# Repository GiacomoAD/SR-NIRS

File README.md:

# SR-NIRS
> Started on Jan/2021

SR-NIRS is a project to develop a low cost, portable, Spatially Resolved Near-Infrared Spectroscopy embedded system. Currently, the project is based on ESP-32 microcontroller.

The goal is to be able to monitor Tissue Oxygenation Index (TOI) from the forearm muscle during arm arterial occlusion experiment in a real time application.

The project also includes the development of a *Python GUI* to interact with the system.

*Undergraduate Final Project*

## Python GUI

This system was developed along with a Python GUI to enable wireless (currently Bluetooth) communication and data logging, as well as user monitoring of the incoming NIRS signal.

****

### Setup - Python Virtual Environment  

**This step, even though recommended, is not required. You can skip to Python Requirements sections if you wish.**

First of all, it is recommended to create a Python Virtual Environment. This can be done through python's embedded  (v. 3.4+) module called **venv**:

```
python -m venv [directory]
``` 

Then, the environment should be activated through:  
- ### Windows  
``` 
[directory]\Scripts\activate.bat
```

- ### Linux or MacOS  
```
source [directory]/bin/activate 
``` 

[More information on python virtual environments can be found here.](https://python.land/virtual-environments/virtualenv)

### Setup - Python Requirements

All of the required packages are included on **_requirements.txt_** file, inside **_GUI_** folder.  

These requirements can be installed through python's **pip** module, as it follows:

```
pip install -r requirements.txt
``` 

### Running GUI

To run the system GUI, the **_main.py_** script should be executed:
```
python main.py
``` 

***
## Documentation

The documentation will be in included in this repository as the project progresses.

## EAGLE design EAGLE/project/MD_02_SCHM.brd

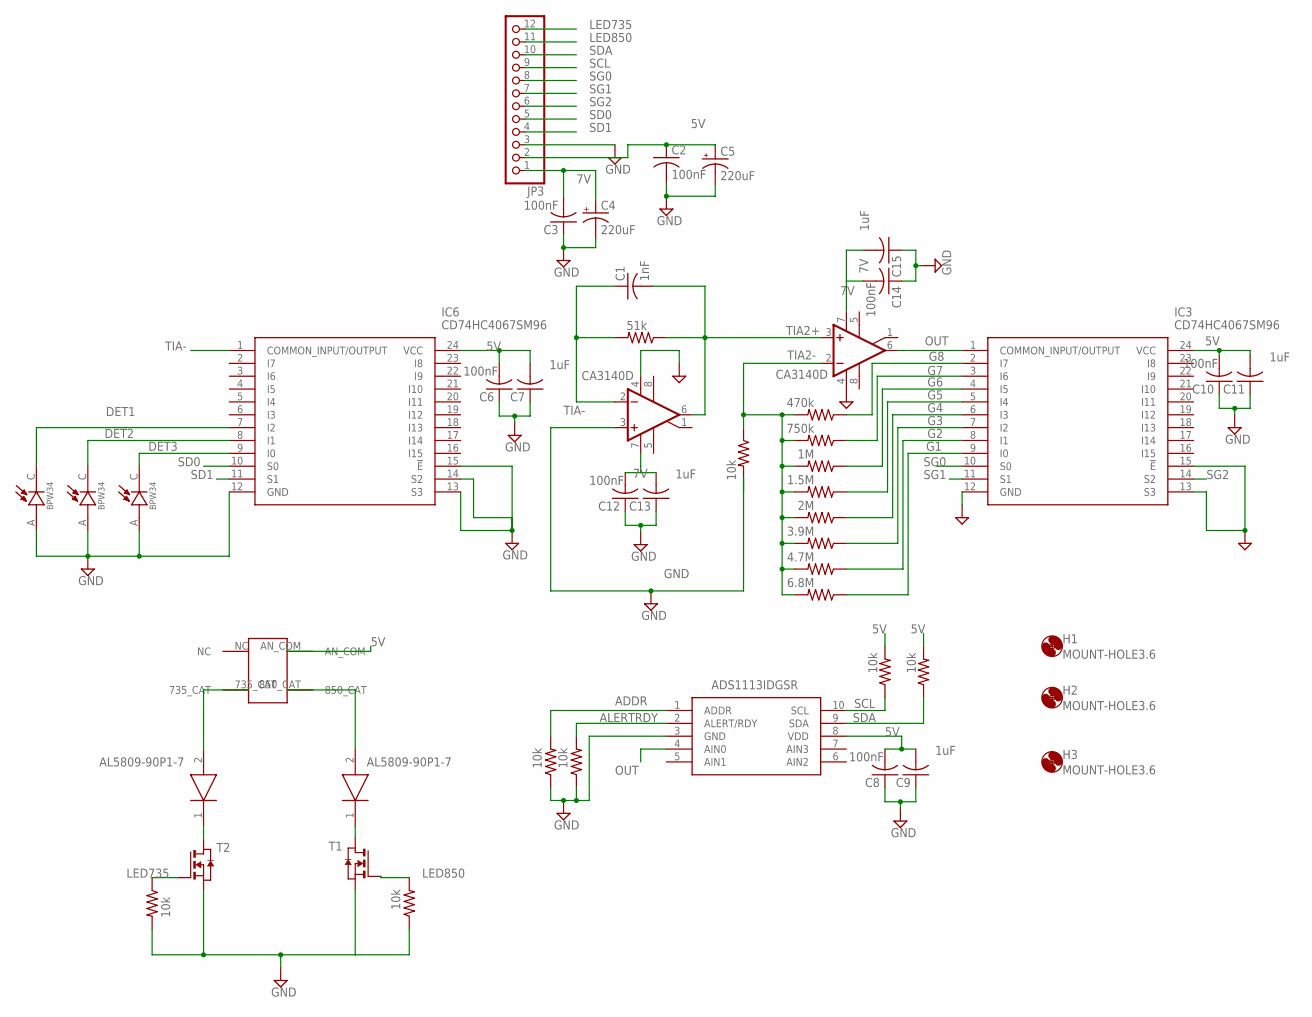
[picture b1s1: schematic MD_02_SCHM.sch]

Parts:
C1: 1nF; C0805
C2, C3, C6, C8, C10, C12, C14: 100nF; C0805
C4, C5: 220uF; E5-6
C7, C9, C11, C13, C15: 1uF; C0805
D1, D5: AL5809-90P1-7; SODFL3718X100N
D2, D3, D4: BPW34; DIO_BPW34
H1, H2, H3: MOUNT-HOLE3.6; 3,6
IC1, IC2: CA3140D; SO08
IC3, IC6: CD74HC4067SM96; SOP65P780X200-24N
IC5: ADS1113IDGSR; SOP50P490X110-10N
JP3: PINHD-1X12; 1X12
R1: 51k; R0805
R2, R11, R12, R13, R14, R15, R16: 10k; R0805
R3: 470k; R0805
R4: 750k; R0805
R5: 1M; R0805
R6: 1.5M; R0805
R7: 2M; R0805
R8: 3.9M; R0805
R9: 4.7M; R0805
R10: 6.8M; R0805
T1, T2: NMOSSOT23; SOT-23
U$1: SMT735D_850D

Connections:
5V: C2.1, C5.+, C6.2, C7.2, C8.2, C9.2, C10.2, C11.2, IC3.24 (VCC), IC5.8 (VDD), IC6.24 (VCC), JP3.2, R13.2, R14.2, U$1.AN_COM
7V: C3.2, C4.+, C12.2, C13.2, C14.2, C15.2, IC1.7 (V+), IC2.7 (V+), JP3.1
ADDR: IC5.1 (ADDR), R11.2
ALERTRDY: IC5.2 (ALERT/RDY), R12.2
DET1: D2.C, IC6.7 (I2)
DET2: D3.C, IC6.8 (I1)
DET3: D4.C, IC6.9 (I0)
G1: IC3.9 (I0), R10.1
G2: IC3.8 (I1), R9.1
G3: IC3.7 (I2), R8.1
G4: IC3.6 (I3), R7.1
G5: IC3.5 (I4), R6.1
G6: IC3.4 (I5), R5.1
G7: IC3.3 (I6), R4.1
G8: IC3.2 (I7), R3.1
GND: C2.2, C3.1, C4.-, C5.-, C6.1, C7.1, C8.1, C9.1, C10.1, C11.1, C12.1, C13.1, C14.1, C15.1, D2.A, D3.A, D4.A, IC1.3 (+IN), IC1.4 (V-), IC2.4 (V-), IC3.12 (GND), IC3.13 (S3), IC3.15 (!E), IC5.3 (GND), IC6.12 (GND), IC6.13 (S3), IC6.14 (S2), IC6.15 (!E), JP3.3, R2.2, R11.1, R12.1, R15.2, R16.1, T1.2 (S), T2.2 (S)
LED735: JP3.12, R15.1, T2.3 (G)
LED850: JP3.11, R16.2, T1.3 (G)
unnamed: D5.1 (K), T2.1 (D)
unnamed: D1.1 (K), T1.1 (D)
unnamed: D1.2 (A), U$1.850_CAT
unnamed: D5.2 (A), U$1.735_CAT
OUT: IC2.6 (OUT), IC3.1 (COMMON_INPUT/OUTPUT), IC5.4 (AIN0)
SCL: IC5.10 (SCL), JP3.9, R13.1
SD0: IC6.10 (S0), JP3.5
SD1: IC6.11 (S1), JP3.4
SDA: IC5.9 (SDA), JP3.10, R14.1
SG0: IC3.10 (S0), JP3.8
SG1: IC3.11 (S1), JP3.7
SG2: IC3.14 (S2), JP3.6
TIA2+: C1.2, IC1.6 (OUT), IC2.3 (+IN), R1.1
TIA2-: IC2.2 (-IN), R2.1, R3.2, R4.2, R5.2, R6.2, R7.2, R8.2, R9.2, R10.2
TIA-: C1.1, IC1.2 (-IN), IC6.1 (COMMON_INPUT/OUTPUT), R1.2

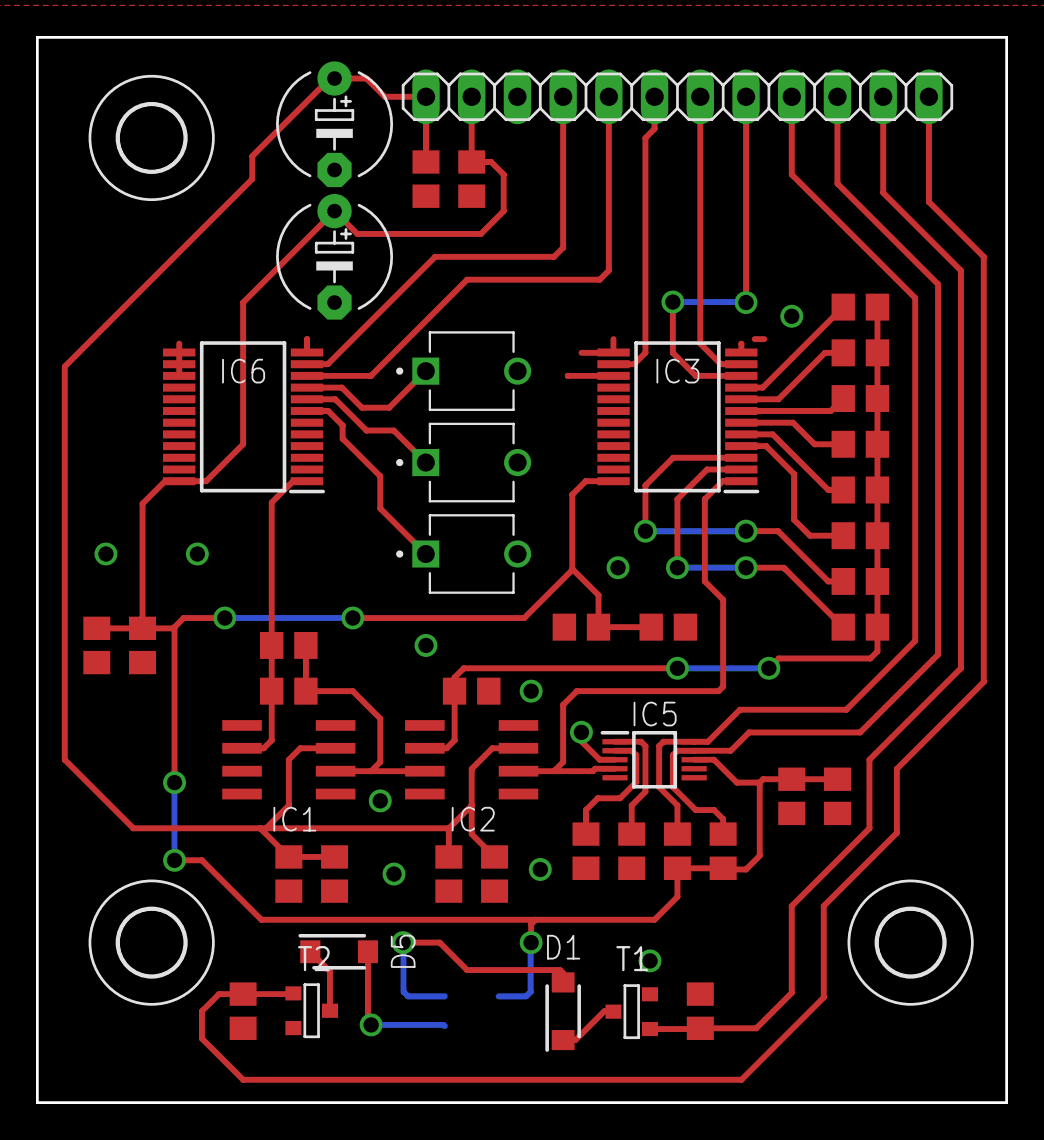
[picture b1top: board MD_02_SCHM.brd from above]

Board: 2 copper layers, 53.8 x 59.2 mm, 48 parts (1 on the bottom side), 33 nets.

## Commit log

2021-06-29 Work in progress. Stable 3 channel version. GUI plotting needs to be fixed, but data is logged on PC.
2021-07-02 Trigger button working. Logs and triggers are saved on timestamped folders. User can choose experiment logging folder.
2021-07-06 Adding CD74HC Multiplexer library
2021-07-06 LED multiplexing class for SR NIRS project
2021-07-09 SR NIRS Sensor class
2021-07-14 Changes to variables scope
2021-07-14 Including new SRSensor class and main app. Now auto-gain calibration works with all 3 channels.
2021-07-21 Removing unused stuff from code
2021-07-22 New closeEvent (saving .nirs file as matlab object). NIRSFormatter file included.
2021-07-22 Configuration messages now have #C as prefix
2021-07-22 Commenting code
2021-07-22 Removing unecessary stuff
2021-07-22 Including used libs
2021-07-27 Bluetooth start acquisition button is now properly handled
2021-07-27 Console log text can now be cleared with #C command
2021-07-28 Plotting now working for 1 channel.
2021-07-29 Python package requirements list
2021-07-29 Changes to Channel Config Panel qtItems names
2021-07-29 Channel configuration combo box now working. Current settings displayed on configuration text field
2021-07-29 Adding resources references for icons folder
2021-07-29 Fixed missing parameter on readFromFile
2021-07-29 Fixing plot file path related issues
2021-07-29 Updated README with GUI installation guide
2021-07-29 Fixing typos
2021-07-30 System now notifies GUI when BT is connected. GUI serial handling adjusted.
2021-07-30 Notifying GUI upon BT Connection
2021-07-31 New SRBluetooth library added
2021-07-31 Changes to use SRBluetooth library
2021-08-03 New utility_functions.py module. Some functions were moved there to improve code organization; main.py changed accordingly.
2021-08-03 User can now choose to display different or multiple channels at once
2021-08-12 Autoscaling for all channels
2021-08-12 Visible channel is now working properly
2021-08-15 Including HX711 module library
2021-08-15 Pressure sensor reading through HX711 module testing sketch
2021-08-15 Separating libraries from sketches
2021-08-16 Adding EAGLE files
2021-08-17 Updating EAGLE files and top/bottom layers PDF
2021-08-25 Updated vias diameter and MUX footprint; Added GND vias; Polygon isolation changed to 24
2021-08-25 Updating layers PDF
2021-08-25 Updating CAMOutputs to match updated project
2021-11-19 Adding PCB test sketch
2021-11-19 Add files via upload
    Adding PCB test sketch
2022-01-06 Adding SR Sensor schematic
2022-01-06 Updating Layers PDF files
2022-01-07 Including SRPRessure library
2022-01-26 Read commands method and clear buffer implemented
2022-01-26 RunVOT method implemented
2022-01-26 Main now runs both sensor reading and VOT
2022-01-26 Adding VOT functionalities to GUI
2022-01-27 Allowing for user VOT pressure input and sending arm cuff pressure back to GUI
2022-01-27 Added pressure input and display on monitoring tab
2022-01-27 Changes to allow pressure input from user and pressure display
2022-01-27 Will not display negative pressure values
2023-04-03 Adding the final report
